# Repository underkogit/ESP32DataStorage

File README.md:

# ESP32 Data Storage — HTTP API

Веб-сервис на ESP32 (порт **80**), работающий с SD-картами по SPI. Все данные отдаются/принимаются по HTTP: просмотр карточек и файлов, плавное получение размеров, скачивание, загрузка, дозапись строк логов (для второго ESP) и удаление.

Страница интерфейса открывается на корне: `http://192.168.0.104/` — любой неизвестный путь тоже отдаёт её.

---

## Общие правила

### Параметр `card`
Все эндпоинты адресуются к карте памяти через параметр **`card`** — индекс SD-карты (список и порядок возвращает `/api/cards`):
- если параметр опущен — используется карта `0`;
- несуществующий индекс → `404 {"error":"card not found"}`;
- карта не готова (вышла, не смонтировалась) → `503 {"error":"storage not ready"}`.

### Пути
- Путь всегда **начинается с `/`** и передаётся **URL-кодированным** (пробел → `%20`, кириллица → `%D0%B0...`).
- `..` в путях запрещён → `400 {"error":"invalid path"}`.
- Имена файлов UTF-8/длинные имена FAT поддерживаются.

### Формат ошибок
Единообразный JSON c HTTP-кодом:

```
HTTP/1.1 404 Not Found
{"error":"file not found"}
```

| Код | Когда |
|-----|-------|
| 400 | неверные параметры (путь, пустое тело, попытка удалить корень) |
| 404 | карта/файл/папка не найдены |
| 500 | ошибка записи/удаления на стороне ESP32 |
| 503 | карта не готова (unmounted/not ready) |

### Особенности сервера (важно знать клиенту)
- Сервер **однопоточный и блокирующий**: пока идёт скачивание большого файла, остальные запросы ждут своей очереди. Логи (`/api/append` с частотой единицы мс на строку) можно слать постоянно, но не во время 10-мегабайтного скачивания.
- Соединения: ядро WebServer всегда отвечает с `Connection: close` — на каждый запрос создаётся новое TCP-соединение. Это нормально.
- POST-тело хранится в heap ESP32 как C-строка: **нулевые байты (`\0`) обрежут тело** — для текстовых логов это неактуально.

---

## 1. Список карт — `GET /api/cards`

```
GET /api/cards
```

Пример:
```cmd
curl.exe http://192.168.0.104/api/cards
```

```json
{
  "cards": [
    {"index":0,"name":"SD0","ready":true,"totalBytes":15518,"usedBytes":2048,"freeBytes":13470,"type":3},
    {"index":1,"name":"SD1","ready":false}
  ]
}
```

Поля: `name` — имя карты из `config.cpp`; `ready` — смонтирована ли; `type` — тип карточки (`3` = SDHC, `2` = SD, `1` = MMC). Байтовые поля есть только если `ready:true`. Все байты как `uint32` (карты >4 ТБ сюда не поместятся — у нас FAT32, не проблема).

---

## 2. Список файлов — `GET /api/files` (быстрый, без размеров)

```
GET /api/files?card=0&dir=/подпапка
```

| Параметр | Описание |
|----------|----------|
| `card` | индекс карты (по умолчанию `0`) |
| `dir` | **каталог для просмотра**. По умолчанию — `/`. Финальный слэш можно оставить, он срежется |

Отдаёт (только **один уровень**, без рекурсии) имена и тип объектов — **без размеров**. Размеры идут отдельно и плавно: `/api/sizes`.

Пример:
```cmd
curl.exe "http://192.168.0.104/api/files?card=0&dir=/"
```

```json
{
  "card": 0,
  "dir": "/",
  "children": [
    {"name":"logs","path":"/logs","dir":true},
    {"name":"test.txt","path":"/test.txt","dir":false},
    {"name":"IMG_0001.jpg","path":"/IMG_0001.jpg","dir":false}
  ]
}
```

Ответ **потоковый (chunked)** — даже при тысячах объектов ESP32 не забивает heap. Это базовый запрос интерфейса: список появляется почти мгновенно (один проход `readdir` без `stat` на каждый файл).

---

## 3. Плавное получение размеров — `GET /api/sizes`

```
GET /api/sizes?card=0&dir=/&start=0&count=24
```

| Параметр | Описание |
|----------|----------|
| `card`, `dir` | как в `/api/files` |
| `start` | **индекс входа в тот же список `children`** (порядок сохраняется), с которого начать (`0` в первый раз) |
| `count` | сколько обработать за раз (по умолчанию `24`, максимум `64`) |

Возвращает `count` записей: файлам вычислен размер, папкам посчитано количество объектов внутри. **`more` — индекс следующего захода** (`-1` — конец).

```json
{
  "items": [
    {"name":"logs","dir":true,"children":3},
    {"name":"test.txt","dir":false,"size":25},
    {"name":"глючный.tmp","dir":false,"err":true}
  ],
  "more": 24
}
```

`err:true` — объект исчез (удалён/частично недоступен) между запросами; клиент должен **сбросить своё "…"** на этой позиции.

Клиент продолжает запросы с `start = more`, пока `more != -1`. Пример цикла:

```bash
START=0
while :; do
  RESP=$(curl -s "http://192.168.0.104/api/sizes?card=0&dir=/&start=$START&count=24")
  echo "$RESP"   # разбираете JSON, обновляете UI
  START=$(echo "$RESP" | jq -r '.more')
  [ "$START" = "-1" ] && break
done
```

Веб-морда делает это сама, порциями по 24, обновляя ячейки по мере поступления.

---

## 4. Инфо о файле/папке — `GET /api/file/info`

```
GET /api/file/info?card=0&path=/logs/esp2.log
```

```json
{
  "card": 0, "cardName":"SD0",
  "path":"/logs/esp2.log", "name":"esp2.log",
  "dir": false, "size": 1024, "children": 0,
  "totalBytes": 15518, "usedBytes": 2048, "freeBytes": 13470
}
```

Для папки `"dir":true`, `"children"` — число объектов внутри (один обход readdir), `"size"` = 0.

---

## 5. Скачивание — `GET /download`

```
GET /download?card=0&path=/logs/esp2.log
```

Отдаёт файл как `application/octet-stream` c `Content-Disposition: attachment` (браузер предложит сохранить). Размер известен из `Content-Length` — прогресс считается по нему и загруженным байтам.

```cmd
curl.exe -o log.txt "http://192.168.0.104/download?card=0&path=/logs/esp2.log"
```

С прогрессом в браузере (XHR, как в UI):

```js
const xhr = new XMLHttpRequest();
xhr.open('GET', '/download?card=0&path=' + encodeURIComponent(path));
xhr.responseType = 'blob';
xhr.onprogress = ev => console.log((ev.loaded / size * 100).toFixed(0) + '%');
xhr.onload = () => {
  const a = document.createElement('a');
  a.href = URL.createObjectURL(xhr.response);
  a.download = path.split('/').pop();
  a.click();
};
xhr.send();
```

---

## 6. Загрузка файла — `POST /upload`

```
POST /upload?card=0      (multipart/form-data, поле `file`)
```

Пример (curl сохранит файл на карте под его локальным именем):
```cmd
curl.exe -F "file=@C:\path\photo.jpg" "http://192.168.0.104/upload?card=0"
```

PowerShell 7:
```powershell
Invoke-RestMethod -F file=@C:\path\photo.jpg "http://192.168.0.104/upload?card=0"
```

Успех:
```json
{"ok":true,"message":"upload complete"}
```

**Особенность**: файл кладётся в **корень карты** (имя берётся из формы). Вложиться в подпапку можно хитростью — задать путь в `filename`:
```cmd
curl.exe -F "file=@C:\path\photo.jpg;filename=Photos/photo.jpg" "http://192.168.0.104/upload?card=0"
```
(папка `Photos` должна уже существовать).

---

## 7. Дозапись строки лога — `POST /api/append`  ← для второго ESP

```
POST /api/append?card=0&path=/logs/esp2.log      (Content-Type: text/plain)
```

Тело запроса = строка (или строки) лога, пишутся **как есть** в конец файла. Сервер гарантирует `\n` на конце, так что каждый запрос = завершённые строки. Родительские папки (`/logs`) создаются автоматически — клиенту не надо думать о структуре.

```cmd
curl.exe -X POST -H "Content-Type: text/plain" --data "boot OK, rssi=-58" "http://192.168.0.104/api/append?card=0&path=/logs/esp2.log"
```

Ответ:
```json
{"ok":true,"path":"/logs/esp2.log","bytes":17,"size":1024}
```
- `bytes` — сколько дописано;
- `size` — файл **после** дописи.

С **другого ESP32** (Arduino, HTTPClient):

```cpp
#include <HTTPClient.h>

void logToHost(const String& line) {
    HTTPClient http;
    http.begin("http://192.168.0.104/api/append?card=0&path=/logs/esp2.log");
    http.addHeader("Content-Type", "text/plain");
    int code = http.POST(line);        // тело = строка
    http.end();                        // (code == 200 → успех)
}
logToHost("runtime=" + String(millis()));
```

Важные детали:
- **Обязательно `Content-Type: text/plain`** (или любой не-формовый): иначе ядро разберёт тело как form и `plain` останется пустым → `400 empty body`.
- Тело пишется байт-в-байт: `\0` в тексте не отправлять.
- Несколько строк за раз — просто встаёт многострочное тело: `a\nb` → файл получит `a\nb\n`.
- Частота: одно дописывание ≈ единицы мс (open→append→close) — можно слать постоянно.
- В serial-мониторе виден каждый вызов: `[APPEND] /logs/esp2.log: +17 bytes (file size 1024)`.

---

## 8. Удаление — `GET /api/delete`

```
GET /api/delete?card=0&path=/test.txt
```

```json
{"ok":true,"path":"/test.txt","type":"file"}
```

- **Файл** — удаляется сразу.
- **Папка** — удаляется, **только если пустая**. Непустая → `500 {"error":"folder not empty (or delete failed)"}` (защита от сноса дерева).
- Корень `/` удалить нельзя → `400`.
- Папка/файл не существует → `404 not found`.

Пример удалить папку:
```cmd
curl.exe "http://192.168.0.104/api/delete?card=0&path=/tmp_folder"
```

В веб-морде у файлов и папок есть кнопка 🗑 — она откроет confirm и после успеха обновит список.

---

## 9. Логи самого ESP — `/logs/host.log` на карте из config

ESP32 сам пишет журнал всех принятых/отправленных HTTP-запросов и событий (монтирование карт, WiFi, append/delete/download/upload, ошибки). Строки однотипны:

```
[+12.3s] [API] /api/files card=0 dir=/ → 8 items · 41 ms
[+45.8s] [APPEND] card=0 /logs/esp2.log +17 bytes (size 1024)
[+51.2s] [DL] start card=0 /IMG_0001.jpg (60148 bytes)
```

- Метка `[+сек.s]` — время работы ESP (uptime). Файл-host выбирается **в `src/config.cpp`**:
  ```cpp
  const int    LOG_CARD_INDEX     = 0;          // ← карта, куда пишутся логи (индекс из /api/cards)
  const char*  LOG_DIR            = "/logs";
  const char*  LOG_FILE           = "host.log";
  const size_t LOG_MAX_FILE_BYTES = 256 * 1024; // ротация при превышении
  ```
- При превышении `LOG_MAX_FILE_BYTES` текущий `host.log` переезжает в `host.log.1` (хранится одна прошлая копия).
- Пока карта логов не готова — строки уходят в Serial и держатся в RAM-кольце (32 последние).
- `/api/file/info` и оболочка браузера (страница `/`) в журнал не пишутся — там шум.

---

## Сводка эндпоинтов

| Метод | Путь | Назначение |
|-------|------|-----------|
| GET | `/` | веб-интерфейс (и любой другой путь) |
| GET | `/api/cards` | список карт + их состояние |
| GET | `/api/files?card&dir` | быстрый список (один уровень, без размеров) |
| GET | `/api/sizes?card&dir&start&count` | плавный расчёт: размеры файлов / количество объектов у папок |
| GET | `/api/file/info?card&path` | сведения о файле/папке + статистика карты |
| GET | `/download?card&path` | скачать файл (octet-stream + attachment) |
| POST | `/upload?card` | загрузить файл (multipart, поле `file`) — в корень карты |
| POST | `/api/append?card&path` | дозаписать строку(-и) лога (text/plain) |
| GET | `/api/delete?card&path` | удалить файл / пустую папку |
| — | SD `/logs/host.log` | журнал запросов ESP (карта/лимиты — в `config.cpp`, `LOG_*`) |

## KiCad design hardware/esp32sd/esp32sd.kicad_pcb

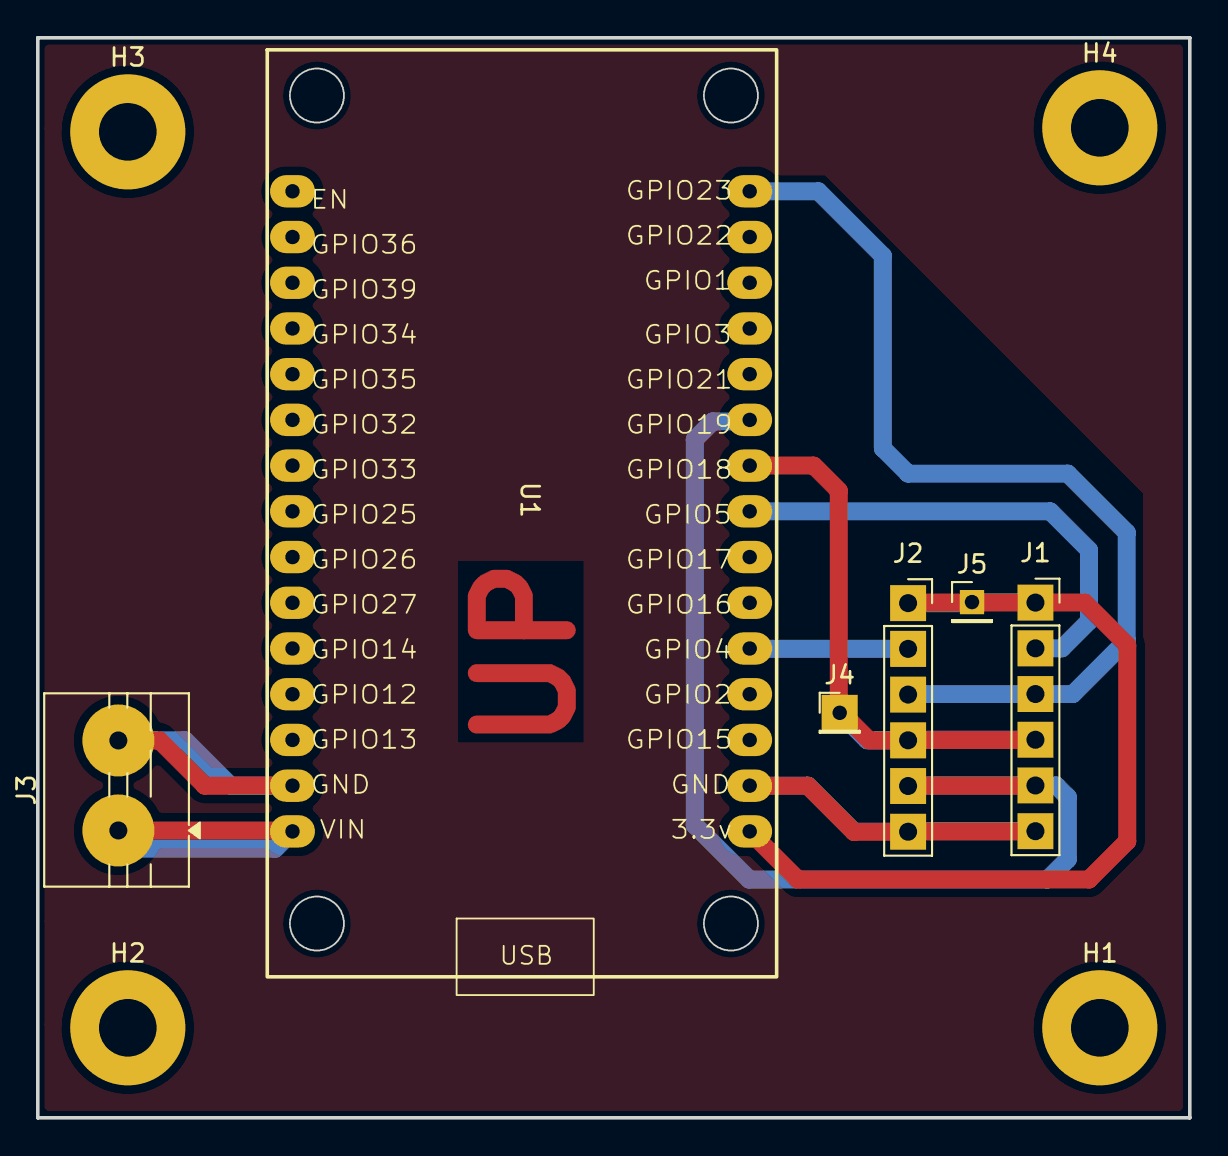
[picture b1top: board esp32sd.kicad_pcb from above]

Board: 2 copper layers, 64.0 x 60.0 mm, 10 parts (0 on the bottom side), 8 nets.

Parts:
H1, H2, H3, H4: MountingHole; MountingHole_3.2mm_M3_Pad
J1, J2: Conn_01x06_Socket; PinSocket_1x06_P2.54mm_Vertical
J3: Screw_Terminal_01x02; TerminalBlock_MaiXu_MX126-5.0-02P_1x02_P5.00mm
J4, J5: Conn_01x01_Pin; PinHeader_1x01_P2.00mm_Vertical
U1: ESP32_30pin

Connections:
3v3: J1.1, J2.1, J5.1 (Pin_1_1), U1.16 (3.3v)
CLK: J1.4, J2.4, J4.1 (Pin_1_1), U1.24 (GPIO18)
CS1: J2.2, U1.20 (GPIO4)
CS2: J1.2, U1.23 (GPIO5)
GND: J1.6, J2.6, J3.2, U1.2 (GND), U1.17 (GND)
MISO: J1.5, J2.5, U1.25 (GPIO19)
MOSI: J1.3, J2.3, U1.30 (GPIO23)
VIN: J3.1, U1.1 (VIN)
